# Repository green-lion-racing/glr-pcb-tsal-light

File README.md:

# glr-pcb-tsal-light

This is a KiCad repository for the TSAL light PCB designed by the Green Lion Racing team.

## Overview

Layout is designed for a (transparent) flex PCB to wrap around the main hoop.

Input is 24V each for red and green LEDs.

LEDs are from Würth Elektronik.

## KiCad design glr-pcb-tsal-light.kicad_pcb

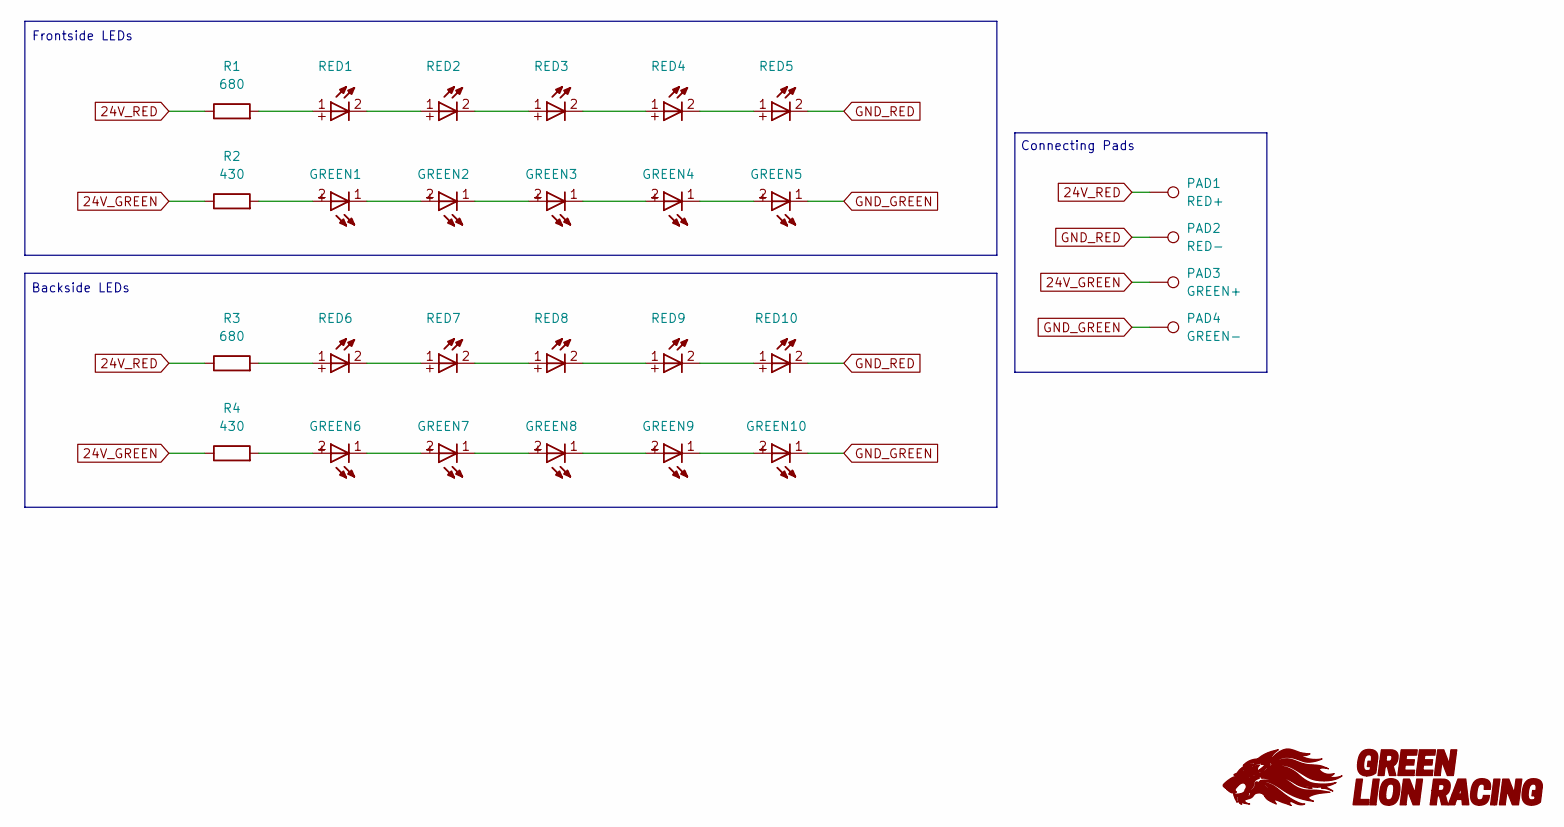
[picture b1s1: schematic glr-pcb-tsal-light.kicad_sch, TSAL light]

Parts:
GREEN1, GREEN2, GREEN3, GREEN4, GREEN5, GREEN6, GREEN7, GREEN8, GREEN9, GREEN10: 2214_150224AS73100; D_Wurth_WL-SMTW-3528; Part Number 150141GS73100
PAD1: RED+; TestPoint_Keystone_5019_Miniature
PAD2: RED-; TestPoint_Keystone_5019_Miniature
PAD3: GREEN+; TestPoint_Keystone_5019_Miniature
PAD4: GREEN-; TestPoint_Keystone_5019_Miniature
R1, R3: 680; R_0805_2012Metric_Pad1.20x1.40mm_HandSolder
R2, R4: 430; R_0805_2012Metric_Pad1.20x1.40mm_HandSolder
RED1, RED2, RED3, RED4, RED5, RED6, RED7, RED8, RED9, RED10: 1608_150160AS73103; D_Wurth_WL-SMTW-3528ADV; Part Number 150141RS73113

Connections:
24V_GREEN: PAD3.1 (1_1), R2.1, R4.1
24V_RED: PAD1.1 (1_1), R1.1, R3.1
GND_GREEN: GREEN5.1 (-), GREEN10.1 (-), PAD4.1 (1_1)
GND_RED: PAD2.1 (1_1), RED5.2 (+), RED10.2 (+)
unnamed: GREEN1.2 (+), R2.2
unnamed: GREEN1.1 (-), GREEN2.2 (+)
unnamed: GREEN2.1 (-), GREEN3.2 (+)
unnamed: GREEN3.1 (-), GREEN4.2 (+)
unnamed: GREEN4.1 (-), GREEN5.2 (+)
unnamed: GREEN6.2 (+), R4.2
unnamed: GREEN6.1 (-), GREEN7.2 (+)
unnamed: GREEN7.1 (-), GREEN8.2 (+)
unnamed: GREEN8.1 (-), GREEN9.2 (+)
unnamed: GREEN9.1 (-), GREEN10.2 (+)
unnamed: RED1.2 (+), RED2.1 (-)
unnamed: R1.2, RED1.1 (-)
unnamed: RED2.2 (+), RED3.1 (-)
unnamed: RED3.2 (+), RED4.1 (-)
unnamed: RED4.2 (+), RED5.1 (-)
unnamed: RED6.2 (+), RED7.1 (-)
unnamed: R3.2, RED6.1 (-)
unnamed: RED7.2 (+), RED8.1 (-)
unnamed: RED8.2 (+), RED9.1 (-)
unnamed: RED9.2 (+), RED10.1 (-)

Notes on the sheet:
Backside LEDs
Connecting Pads
Frontside LEDs

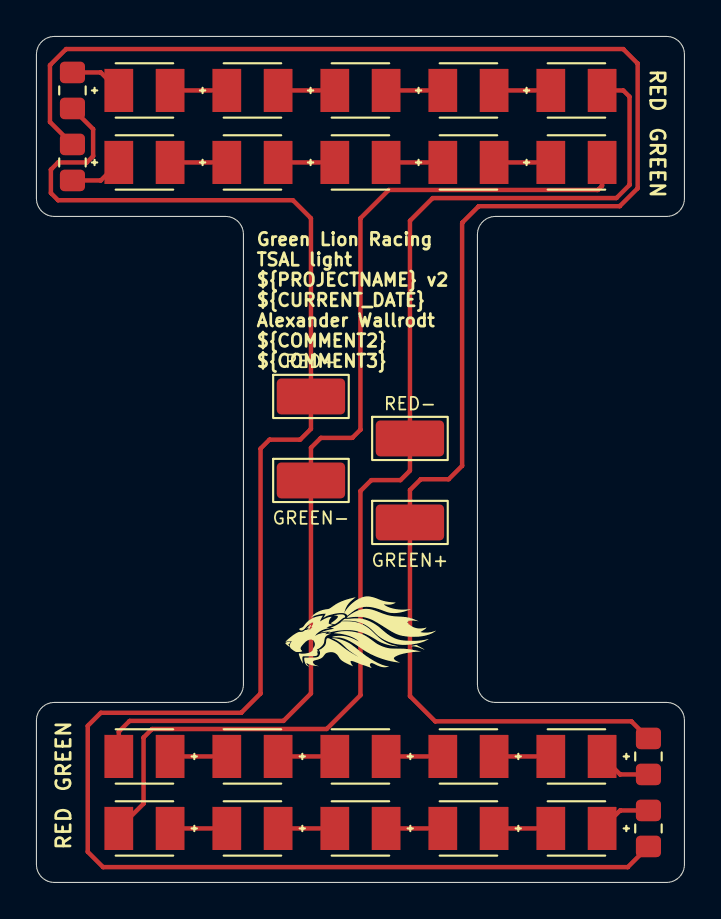
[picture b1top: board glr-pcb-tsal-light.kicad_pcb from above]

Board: 2 copper layers, 36.0 x 47.0 mm, 28 parts (0 on the bottom side), 24 nets.
